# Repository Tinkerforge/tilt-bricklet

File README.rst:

Tilt Bricklet
=============

This repository contains the firmware source code and the hardware design
files. The documentation generator configs can be found at
https://github.com/Tinkerforge/generators

Repository Content
------------------

software/:
 * examples/: Examples for all supported languages
 * build/: Compiled files
 * src/: Source code of firmware
 * Makefile: Makefile to build project

hardware/:
 * Contains KiCad project files and additionally schematics as PDF

datasheets/:
 * Contains datasheets for sensors and complex ICs that are used

Hardware
--------

The hardware is designed with the open source EDA Suite KiCad
(http://www.kicad.org). Before you are able to open the files,
you have to install the Tinkerforge kicad-libraries
(https://github.com/Tinkerforge/kicad-libraries). You can either clone
them directly in hardware/ or clone them in a separate folder and
symlink them into hardware/
(ln -s kicad_path/kicad-libraries project_path/hardware). After that you
can open the .pro file in hardware/ with KiCad and from there view and
modify the schematics and the PCB layout.

Software
--------

If you want to do your own Brick/Bricklet firmware development we highly
recommend that you use our build environment setup script and read the
tutorial (https://www.tinkerforge.com/en/doc/Tutorials/Tutorial_Build_Environment/Tutorial.html).

To compile the C code we recommend you to install the newest GNU Arm Embedded
Toolchain (https://launchpad.net/gcc-arm-embedded/+download).
You also need to install bricklib (https://github.com/Tinkerforge/bricklib)
and brickletlib (https://github.com/Tinkerforge/brickletlib).

You can either clone it directly in software/src/ or clone it in a
separate folder and symlink it into software/src/
(ln -s bricklib_path/bricklib project_path/software/src/ and
ln -s brickletlib_path/brickletlib project_path/software/src/).
Finally make sure to have CMake installed
(http://www.cmake.org/cmake/resources/software.html).

After that you can build the firmware by invoking make in software/.
The firmware (.bin) can then be found in software/build/ and uploaded
with brickv (click button "Flashing" on start screen).

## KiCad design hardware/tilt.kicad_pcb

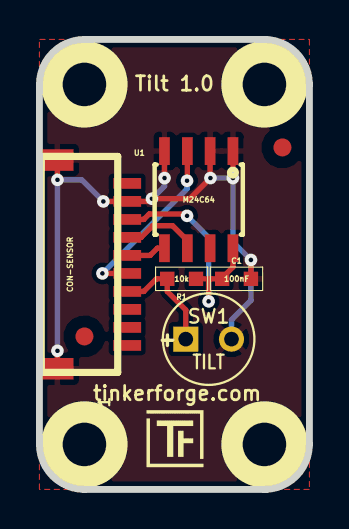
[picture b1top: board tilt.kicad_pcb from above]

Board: 2 copper layers, 15.0 x 25.0 mm, 13 parts (0 on the bottom side), 6 nets.

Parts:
C1: 100nF; 0603
Fiducial_Mark: VAL**; Fiducial_Mark
Fiducial_Mark#2: VAL**; Fiducial_Mark
P1: CON-SENSOR
R1: 10k; 0603
SW1: TILT; C1V5
U1: M24C64; SOIC8
U2, U3, U4, U5: DRILL; DRILL_NP
VAL: WEEE_7mm
VAL#2: CE_5mm

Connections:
GND: C1.2, P1.2, P1.EP, SW1.2, U1.1, U1.2, U1.4
unnamed: P1.4, U1.6
unnamed: P1.6, U1.3
unnamed: P1.5, U1.5
unnamed: P1.7, R1.2, SW1.1
VCC: C1.1, P1.3, R1.1, U1.8

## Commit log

2013-07-23 Initial commit for Tilt Bricklet
2013-08-06 Add callback configuration API, add ClosedVibrating state
2013-08-21 windows: Don't trigger a build in generate_makefile.bat
    Also use normal make instead of a special named one.
2013-09-12 Add examples for Tilt Bricklet
2013-09-17 Fix copy and paste fail
2013-10-15 add hardware files
2014-01-08 python: Fix syntax for Python3
2014-01-08 delphi: Remove empty parentheses
2014-01-10 Add Perl examples
2014-01-14 perl: Fix warning about unsharing the $tilt variable
2014-01-14 perl: Fix duplicate UID
2014-01-15 php: Use const for constant values
2014-02-07 Add Mathematica examples
2014-02-10 perl: fixed namespace and if .. elsif
2014-02-11 javascript: adding examples
2014-02-11 javascript: error message fixed
2014-02-11 javascript: short examples
2014-02-18 javascript: examples fixed
2014-02-20 javascript: add html examples
2014-02-24 javascript: port 4280, startExample()
2014-02-28 javascript: Break long lines and cleanup whitespace
2014-03-05 Add LabVIEW examples
2014-03-06 labview: Add examples in LV2010 format
2014-03-13 heart-rate-bricklet: initial commit
2014-03-13 Revert "heart-rate-bricklet: initial commit"
    This reverts commit 342103e8a31077ffbfca5043518118988c8fca34.
2014-03-25 matlab: add examples
2014-04-02 java: Unify constants style
2014-04-02 Prefer switch over if/else
2014-04-02 perl: Unify print style
2014-04-03 Some whitespace cleanup
2014-04-17 matlab: Adapt examples to new callback style
2014-04-17 matlab: Add parentheses to make pygments happy
2014-07-15 java: Replace System.console() usage with an Eclipse compatible pattern
2014-12-02 Use ReadLine instead of ReadKey for C# example
2015-02-13 vbnet: Use ReadLine instead of ReadKey
    Because ReadKey doesn't work with a pipe as stdin on the RED Brick.
2015-03-02 windows: Stop cmake from searching for mingw32-make.exe
    Using MinGW Makefiles as generator makes cmake search for mingw32-make.exe
    which might not be installed because GnuWin32's make.exe is used instead.
2015-04-09 c: Whitespace
2015-06-24 javascript: Clean up output creation
2015-06-29 octave: Handle short difference between Octave 3.6 and 3.8
    In Octave 3.6 a short is not automatically handled as a number.
2015-07-25 Make JavaScript browser example textarea readonly
2015-07-27 Cleanup C/C++, C#, Java, Python and Ruby examples
2015-07-29 Reformat changelog
2015-08-07 Use full device class name in Python examples
2015-08-12 Fix minor warnings in C/C++ examples
2015-08-17 Cleanup Delphi examples
2015-08-18 Cleanup VB.NET examples
2015-08-18 Fix typo
2015-08-19 Cleanup Perl examples
2015-09-09 Duplicate cmake call to fix bug during cmake creation
2015-10-19 Generator based example cleanup
2015-11-12 matlab: Fix callback handling for R2014a
    http://undocumentedmatlab.com/blog/matlab-callbacks-for-java-events-in-r2014a
2015-11-25 Include date and commit into changelog
2016-05-18 c: Add missing device destroy call
2016-07-01 Make the change UID comment more explicit
2017-04-13 csharp: Adapt example
2017-06-02 octave: Use javaObject instead of deprecated java_new
2017-11-30 Update examples from generator
2017-12-07 mathematica: Also generate .nb files
2018-02-19 javascript: Close div tag correctly
2018-02-20 Cleanup KiCad libraries config
    Ensure LibDir=kicad-libraries and LibName1=tinkerforge.
    Remove special library.
2018-05-24 perl: Use strict in examples
2018-05-28 examples: Unify constant printing style
2018-07-11 Add Makefile with docker support
2018-07-11 Update directory structure and build instructions
2018-07-11 Remove obsolete generate_makefile scripts
2018-11-06 Add rust examples
2018-11-07 rust: Accept host names for ip connection, fix naming inconsistencies
2018-11-07 rust: Rename callback receivers.
2018-12-14 Add go examples.
2018-12-18 go: Change import path.
2018-12-18 go: Change import path again.
2018-12-20 rust: Reformat examples.
2019-01-24 mqtt: Add examples.
2019-01-24 mqtt: Fix example header.
2019-01-24 mqtt: Remove executable bit in example permissions.
2019-01-24 go: Minor example fixes.
2019-01-24 mqtt: Minor example fixes.
2019-03-28 mqtt: Fix whitespace.
2019-08-22 c: Adapt to bindings changes
2020-01-13 examples: Use python3 input instead of python2 raw_input.
2020-01-13 examples: mqtt: Remove trailing whitespace.
2020-03-16 Whitespace
2020-04-07 examples: rust: Always block when calling bindings functions.
2021-10-25 Update KiCad link
    https://www.kicad.org/blog/2021/10/Avoid-links-to-former-kicad-domain/
2022-07-06 Add license files.

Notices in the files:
hardware/tilt.kicad_pcb:
Licensed under CERN OHL v.1.1
Copyright (©) 2013, B.Nordmeyer
Copyright Tinkerforge GmbH 2013.
This documentation describes Open Hardware and is licensed under the
CERN OHL v. 1.1.
